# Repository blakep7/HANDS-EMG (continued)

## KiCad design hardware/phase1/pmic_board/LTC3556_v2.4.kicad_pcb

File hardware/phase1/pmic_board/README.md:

# HANDS-EMG

## Hand Activity Neural Detection using SEMG

## Project Description
A battery-powered surface electromyography (sEMG) sensor system designed to classify hand movements based on the wearer's muscle activity.
The device utilizes four channels of wet electrodes placed on the user's forearm to capture sEMG signals.
These signals are processed through our procured analog front-end module operating at a minimum of 2000 samples per second.
The digitized signals are transmitted to our microcontroller via SPI, where a machine learning algorithm classifies the hand movements based on a pre-trained model.
Our responsibilities include configuring the analog front-end module, programming a low-power microcontroller, integrating the system on a custom PCB, and training the machine learning model for accurate classification.
The system will output the movement classifications via USB, which can be visualized on a PC simulator.
Designed for efficiency, the device operates at a voltage of 3.7V provided by a rechargeable lithium polymer battery for portability.

## Contributors

- Kelly Hubbard
- Noah Marosok
- Blake Pearson
- Jayden Sumbillo
- Kirk Young

## License 📜

This project is licensed under the [Apache License 2.0](LICENSE).

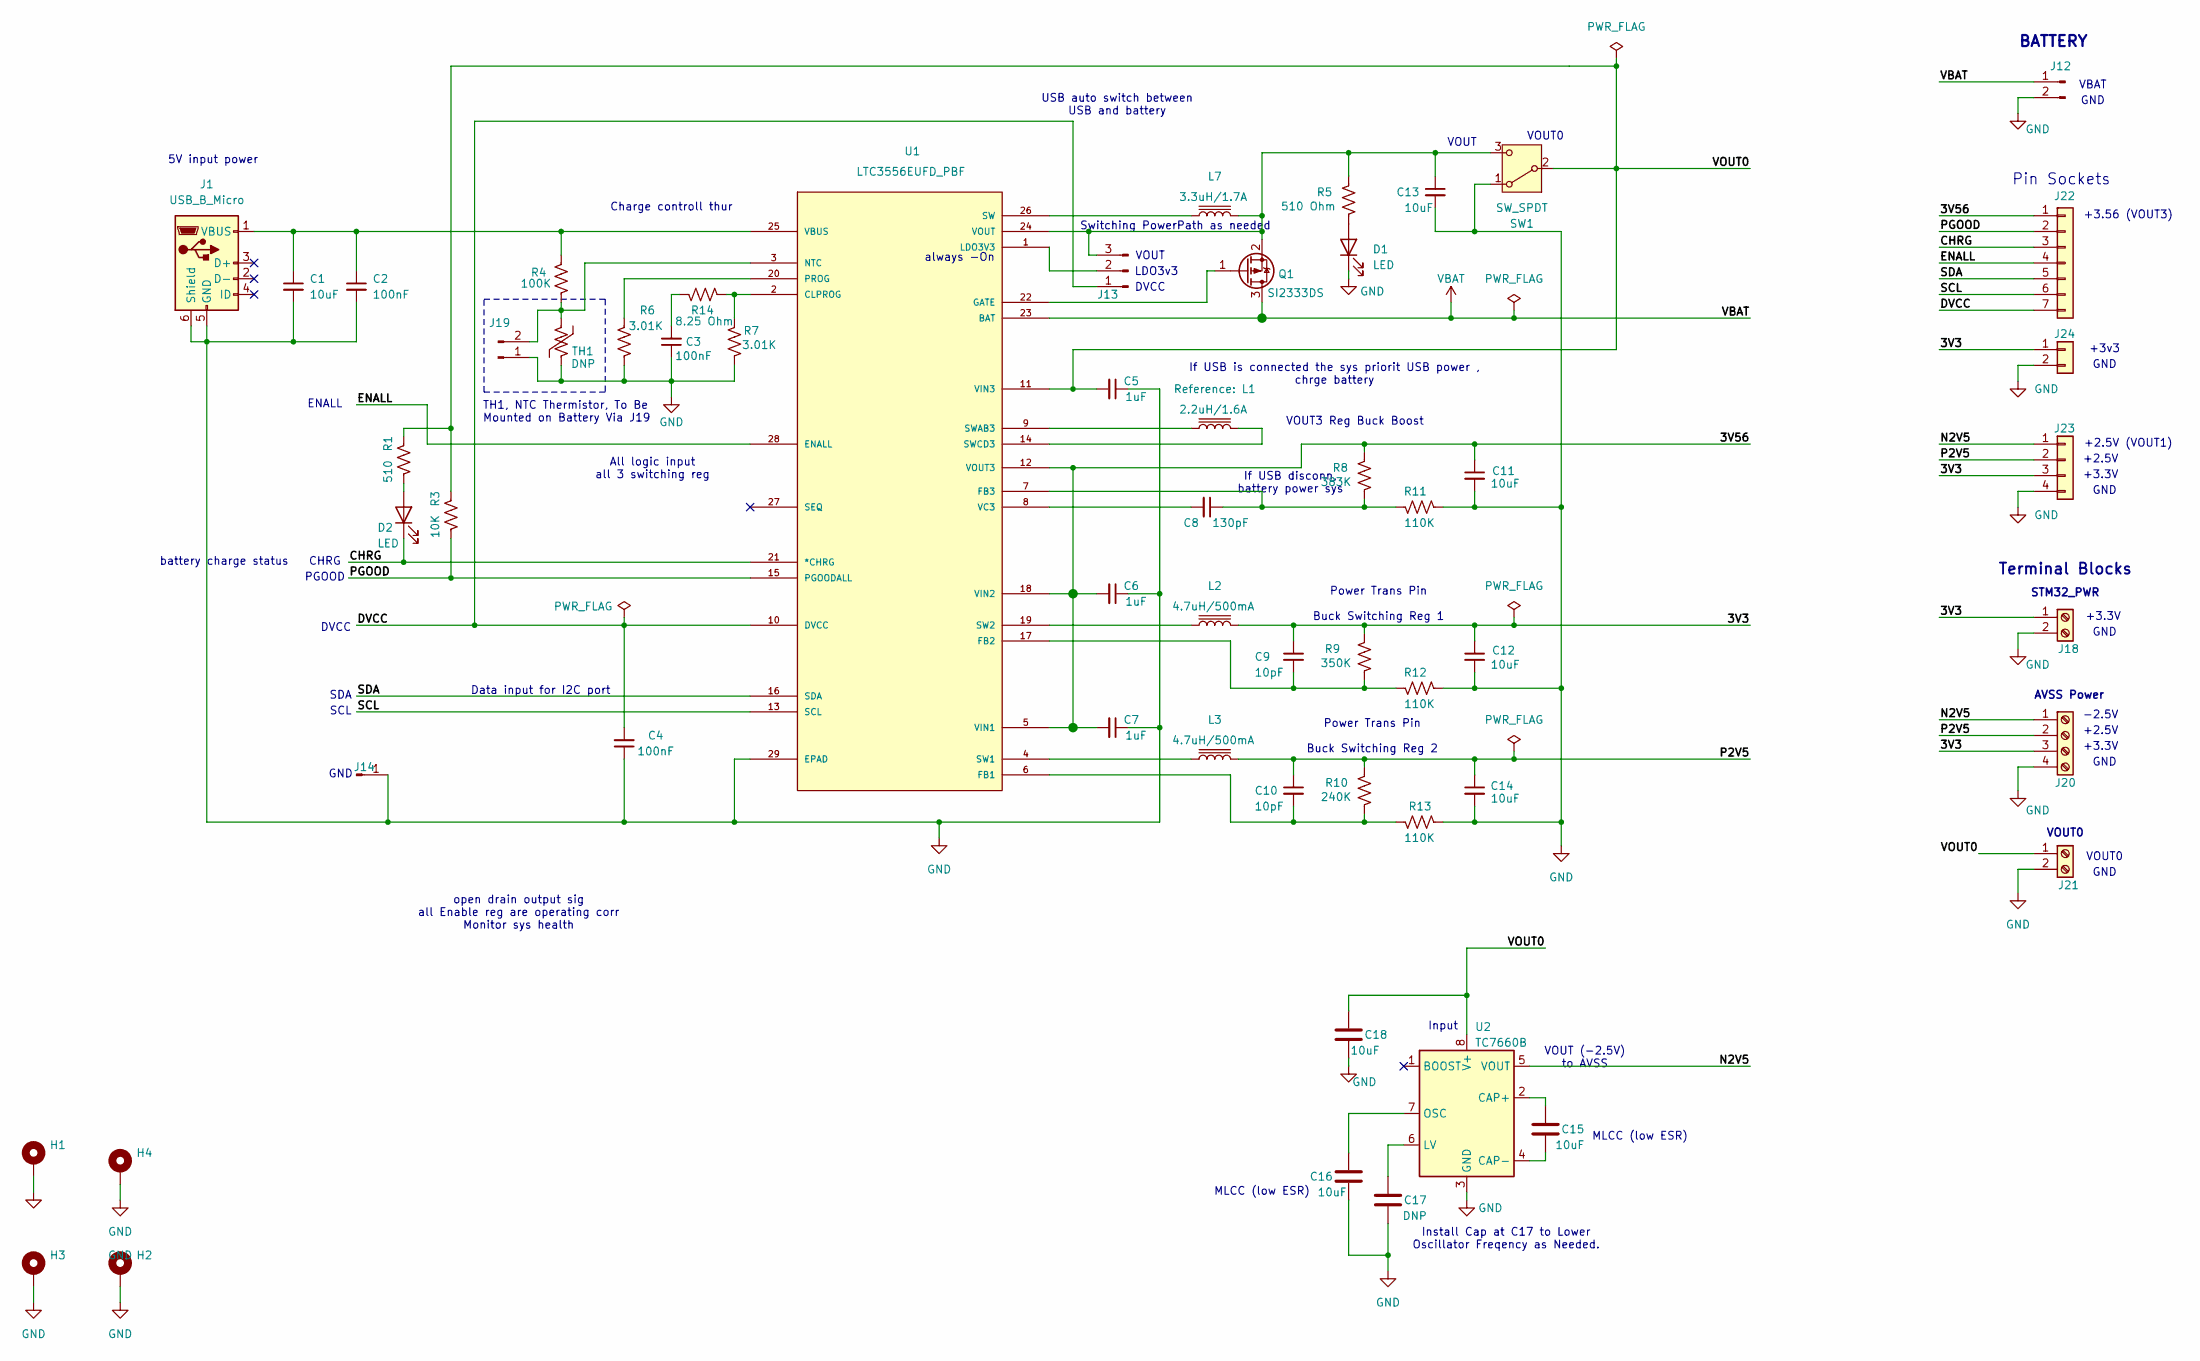
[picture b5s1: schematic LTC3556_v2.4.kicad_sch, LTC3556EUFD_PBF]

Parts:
C1: 10uF; C_1206_3216Metric
C2: 100nF; C_1206_3216Metric
C3, C4: 100nF; C_0402_1005Metric
C5, C6, C7: 1uF; C_0402_1005Metric
C8: 130pF; C_0402_1005Metric
C9, C10: 10pF; C_0402_1005Metric
C11, C12, C13, C14: 10uF; C_0402_1005Metric
C15, C16, C18: 10uF; C_0805_2012Metric_Pad1.18x1.45mm_HandSolder
C17: DNP; C_0805_2012Metric_Pad1.18x1.45mm_HandSolder
D1, D2: LED; LED_0805_2012Metric_Pad1.15x1.40mm_HandSolder
H1, H2, H3, H4: MountingHole_Pad; MountingHole_3.5mm_Pad_TopBottom
J1: USB_B_Micro; USB_Micro-B_Amphenol_10118194-0001LF_Horizontal; MPN C10418
J12: Conn_01x02_Pin; JST_PH_S2B-PH-K_1x02_P2.00mm_Horizontal; MPN C173752
J13: Conn_01x03_Pin; PinHeader_1x03_P2.54mm_Vertical; MPN C49257
J14: Conn_01x01_Pin; PinHeader_1x01_P2.54mm_Vertical; MPN C492400
J18, J21: Screw_Terminal_01x02; TerminalBlock_Phoenix_MPT-0,5-2-2.54_1x02_P2.54mm_Horizontal; MPN C474920
J19: Conn_01x02_Pin; PinHeader_1x02_P2.54mm_Vertical; MPN C225477
J20: Screw_Terminal_01x04; TerminalBlock_Phoenix_MPT-0,5-4-2.54_1x04_P2.54mm_Horizontal; MPN C474922
J22: Conn_01x07; PinSocket_1x07_P2.54mm_Vertical; MPN C2832270
J23: Conn_01x04; PinSocket_1x04_P2.54mm_Vertical; MPN C2685089
J24: Conn_01x02; PinSocket_1x02_P2.54mm_Vertical; MPN C49661
L1: 2.2uH/1.6A; L_Coilcraft_LPS4018
L2, L3: 4.7uH/500mA; L_Coilcraft_LPS3010
L7: 3.3uH/1.7A; L_Coilcraft_LPS4018
Q1: SI2333DS; SOT-23
R1: 510; R_0402_1005Metric_Pad0.72x0.64mm_HandSolder
R3: 10K; R_0402_1005Metric_Pad0.72x0.64mm_HandSolder
R4: 100K; R_0402_1005Metric_Pad0.72x0.64mm_HandSolder
R5: 510 Ohm; R_0402_1005Metric_Pad0.72x0.64mm_HandSolder
R6, R7: 3.01K; R_0402_1005Metric_Pad0.72x0.64mm_HandSolder
R8: 383K; R_0402_1005Metric_Pad0.72x0.64mm_HandSolder
R9: 350K; R_0603_1608Metric
R10: 240K; R_0402_1005Metric_Pad0.72x0.64mm_HandSolder
R11, R12, R13: 110K; R_0402_1005Metric_Pad0.72x0.64mm_HandSolder
R14: 8.25 Ohm; R_0402_1005Metric_Pad0.72x0.64mm_HandSolder
SW1: SW_SPDT; SW_Slide_SPDT_Straight_CK_OS102011MS2Q; MPN C480342
TH1: DNP; C_Disc_D3.0mm_W1.6mm_P2.50mm
U1: LTC3556EUFD_PBF; QFN-28-1EP_4x5mm_P0.5mm_EP2.65x3.65mm_ThermalVias; MANUFACTURER_PART_NUMBER ltc3556eufd#pbf; DigiKey_Part_Number 505-LTC3556EUFD#PBF-ND
U2: TC7660B; SOIC-8_3.9x4.9mm_P1.27mm; MPN C512761

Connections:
/3V3: C9.1, C12.1, J18.1, J20.3, J23.3, J24.1, L2.1, R9.1
/3V56: C6.2, C7.2, C11.1, J22.1, R8.1, U1.5 (VIN1), U1.12 (VOUT3), U1.18 (VIN2)
/CHRG: D2.1 (K), J22.3, U1.21 (*CHRG)
/DVCC: C4.2, J13.1, J22.7, U1.10 (DVCC)
/ENALL: J22.4, U1.28 (ENALL)
/N2V5: J20.1, J23.1, U2.5 (VOUT)
/P2V5: C10.1, C14.1, J20.2, J23.2, L3.1, R10.1
/PGOOD: J22.2, R3.2, U1.15 (PGOODALL)
/SCL: J22.6, U1.13 (SCL)
/SDA: J22.5, U1.16 (SDA)
/VOUT0: C5.2, C18.1, J21.1, R1.1, R3.1, SW1.2 (B), U1.11 (VIN3), U2.8 (V+)
GND: C1.2, C2.2, C3.1, C4.1, C5.1, C6.1, C7.1, C11.2, C12.2, C13.2, C14.2, C16.1, C17.2, C18.2, D1.1 (K), H1.1, H2.1, H3.1, H4.1, J1.5 (GND), J1.6 (Shield), J12.2, J14.1, J18.2, J19.1, J20.4, J21.2, J23.4, J24.2, R6.2, R7.2, R11.2, R12.2, R13.2, SW1.1 (A), TH1.1, U1.29 (EPAD), U2.3 (GND)
unnamed: C3.2, R14.2
unnamed: D1.2 (A), R5.2
unnamed: D2.2 (A), R1.2
unnamed: C1.1, C2.1, J1.1 (VBUS), R4.1, U1.25 (VBUS)
unnamed: J13.2, U1.1 (LDO3V3)
unnamed: C13.1, J13.3, L7.1, Q1.2 (S), R5.1, SW1.3 (C), U1.24 (VOUT)
unnamed: J19.2, R4.2, TH1.2, U1.3 (NTC)
unnamed: Q1.1 (G), U1.22 (GATE)
unnamed: R7.1, R14.1, U1.2 (CLPROG)
unnamed: C10.2, R10.2, R13.1, U1.6 (FB1)
unnamed: C9.2, R9.2, R12.1, U1.17 (FB2)
unnamed: C8.1, R8.2, R11.1, U1.7 (FB3)
unnamed: R6.1, U1.20 (PROG)
unnamed: L3.2, U1.4 (SW1)
unnamed: L2.2, U1.19 (SW2)
unnamed: L7.2, U1.26 (SW)
unnamed: L1.2, U1.9 (SWAB3)
unnamed: L1.1, U1.14 (SWCD3)
unnamed: C8.2, U1.8 (VC3)
unnamed: C15.1, U2.2 (CAP+)
unnamed: C15.2, U2.4 (CAP-)
unnamed: C17.1, U2.6 (LV)
unnamed: C16.2, U2.7 (OSC)
VBAT: J12.1, Q1.3 (D), U1.23 (BAT)

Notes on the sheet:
Power Trans Pin Buck Switching Reg 2
GND
+3.3V
Charge controll thur
Data input for I2C port
VOUT
AVSS Power
+2.5V
LDO3v3
BATTERY
VOUT
SDA
If USB is connected the sys priorit USB power , chrge battery
Input
MLCC (low ESR)
VOUT0
+3v3
always -On
DVCC
-2.5V
All logic input all 3 switching reg
SCL
TH1, NTC Thermistor, To Be Mounted on Battery Via J19
Terminal Blocks
5V input power
VBAT
USB auto switch between USB and battery
Switching PowerPath as needed
Power Trans Pin Buck Switching Reg 1
VOUT (-2.5V) to AVSS
If USB disconn, battery power sys
Pin Sockets
Install Cap at C17 to Lower Oscillator Freqency as Needed.
open drain output sig all Enable reg are operating corr Monitor sys health
+3.56 (VOUT3)
ENALL
STM32_PWR
battery charge status
PGOOD
+2.5V (VOUT1)

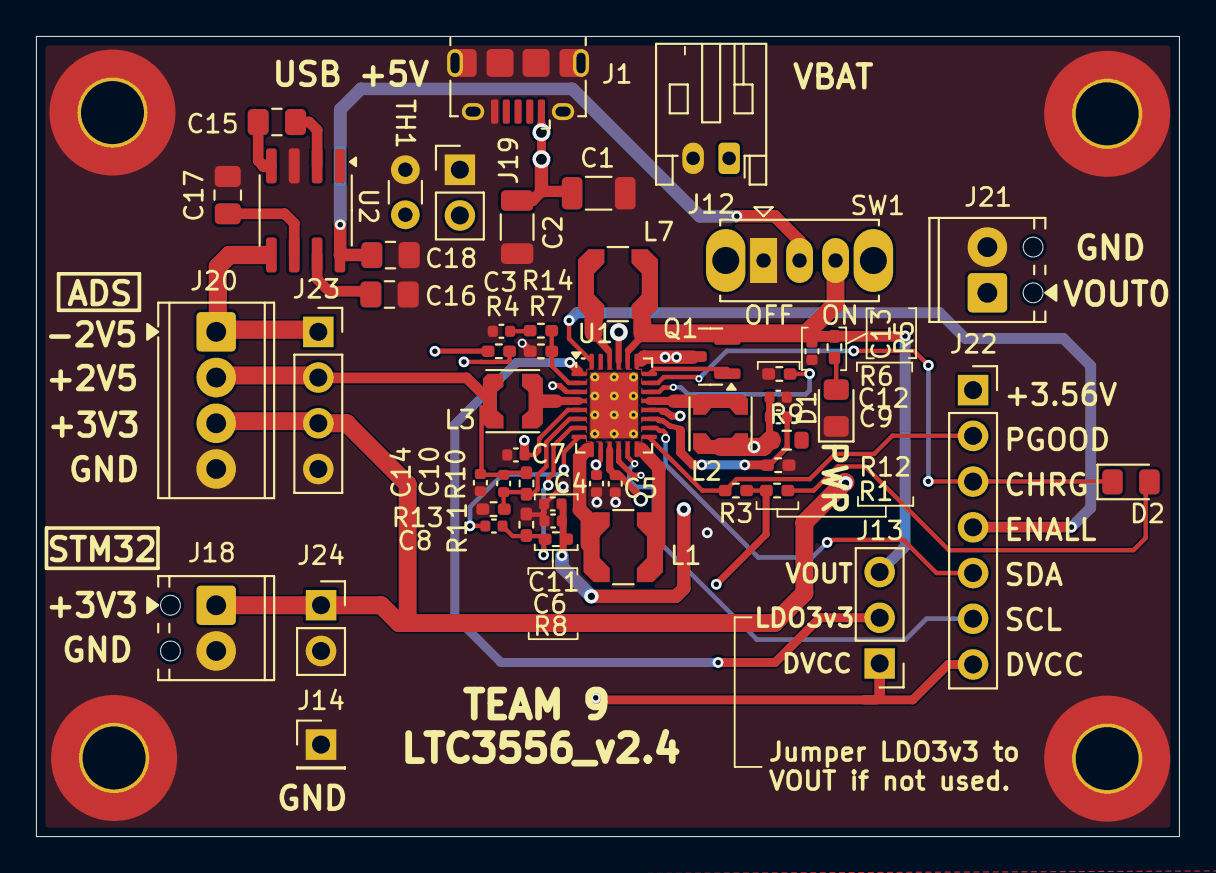
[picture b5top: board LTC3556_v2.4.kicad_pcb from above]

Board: 4 copper layers, 63.5 x 44.5 mm, 57 parts (0 on the bottom side), 36 nets.

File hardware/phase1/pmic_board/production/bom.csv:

Designator,Footprint,Quantity,Value,LCSC Part #
C1,1206,1,10uF,
"C10, C9",0402,2,10pF,
"C11, C12, C13, C14",0402,4,10uF,
"C15, C16, C18",0805,3,10uF,
C2,1206,1,100nF,
"C3, C4",0402,2,100nF,
"C5, C6, C7",0402,3,1uF,
C8,0402,1,130pF,
"D1, D2",0805,2,LED,
J1,USB_Micro-B_Amphenol_10118194-0001LF_Horizontal,1,USB_B_Micro,C10418
J12,JST_PH_S2B-PH-K_1x02_P2.00mm_Horizontal,1,Conn_01x02_Pin,C173752
J13,PinHeader_1x03_P2.54mm_Vertical,1,Conn_01x03_Pin,C49257
J14,PinHeader_1x01_P2.54mm_Vertical,1,Conn_01x01_Pin,C492400
"J18, J21","TerminalBlock_Phoenix_MPT-0,5-2-2.54_1x02_P2.54mm_Horizontal",2,Screw_Terminal_01x02,C474920
J19,PinHeader_1x02_P2.54mm_Vertical,1,Conn_01x02_Pin,C225477
J20,"TerminalBlock_Phoenix_MPT-0,5-4-2.54_1x04_P2.54mm_Horizontal",1,Screw_Terminal_01x04,C474922
J22,PinSocket_1x07_P2.54mm_Vertical,1,Conn_01x07,C2832270
J23,PinSocket_1x04_P2.54mm_Vertical,1,Conn_01x04,C2685089
J24,PinSocket_1x02_P2.54mm_Vertical,1,Conn_01x02,C49661
L1,L_Coilcraft_LPS4018,1,2.2uH/1.6A,
"L2, L3",L_Coilcraft_LPS3010,2,4.7uH/500mA,
L7,L_Coilcraft_LPS4018,1,3.3uH/1.7A,
Q1,SOT-23,1,SI2333DS,
R1,0402,1,510,
R10,0402,1,240K,
"R11, R12, R13",0402,3,110K,
R14,0402,1,8.25 Ohm,
R3,0402,1,10K,
R4,0402,1,100K,
R5,0402,1,510 Ohm,
"R6, R7",0402,2,3.01K,
R8,0402,1,383K,
R9,0603,1,350K,
SW1,SW_Slide_SPDT_Straight_CK_OS102011MS2Q,1,SW_SPDT,C480342
U1,QFN-28-1EP_4x5mm_P0.5mm_EP2.65x3.65mm_ThermalVias,1,LTC3556EUFD_PBF,C685032
U2,SOIC-8_3.9x4.9mm_P1.27mm,1,TC7660B,C512761

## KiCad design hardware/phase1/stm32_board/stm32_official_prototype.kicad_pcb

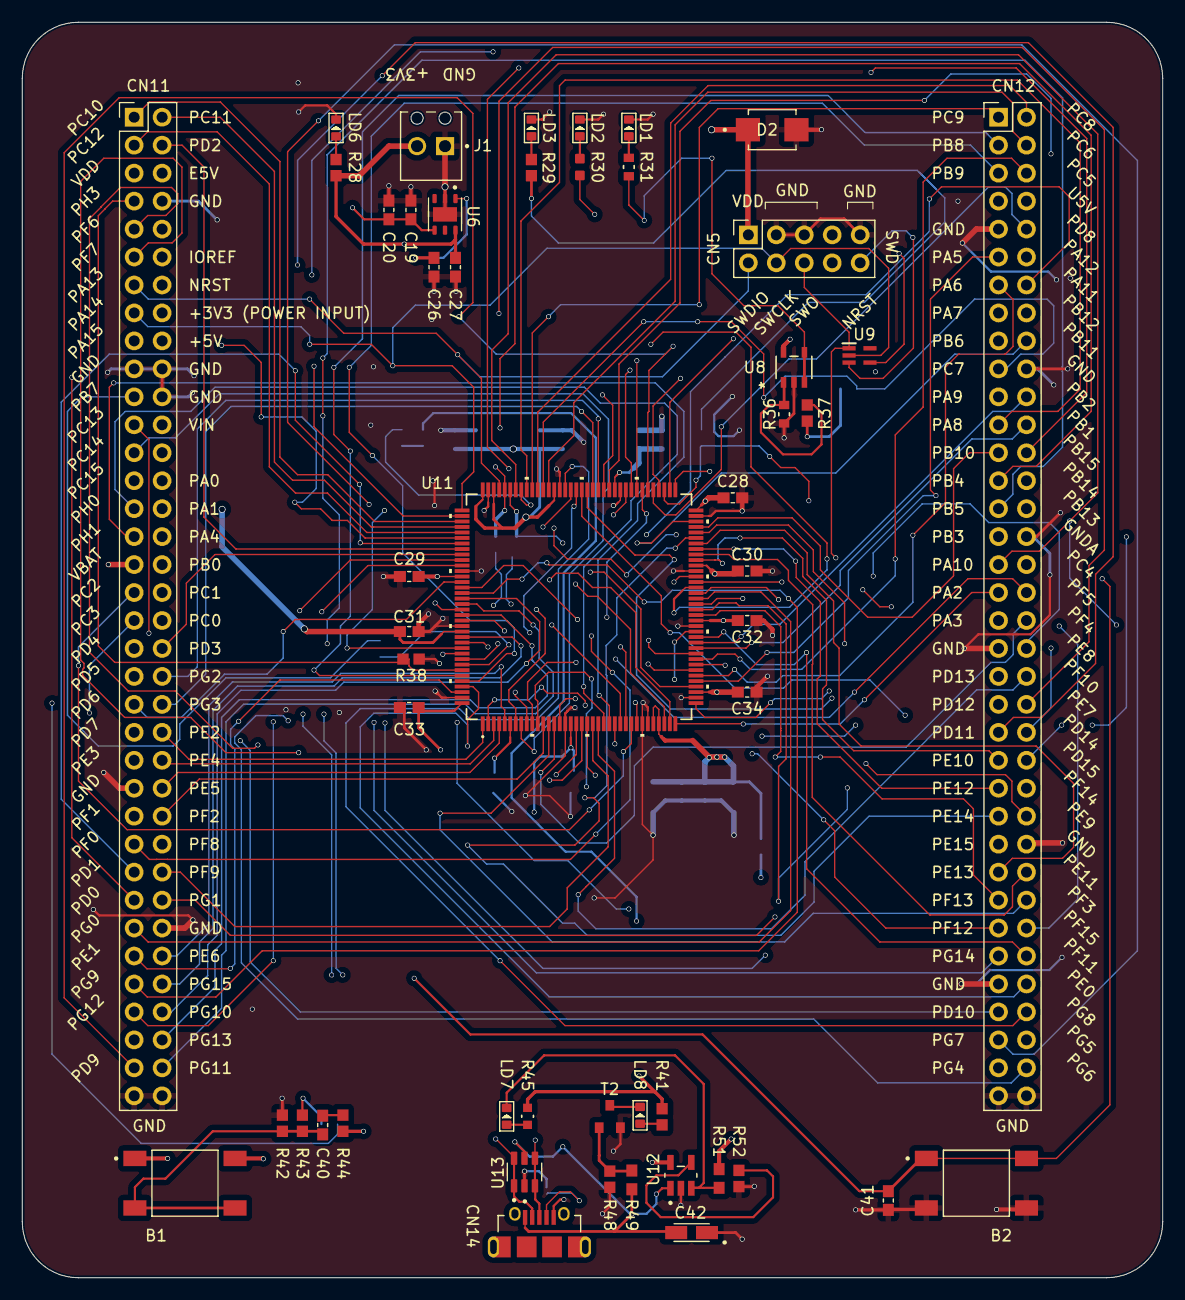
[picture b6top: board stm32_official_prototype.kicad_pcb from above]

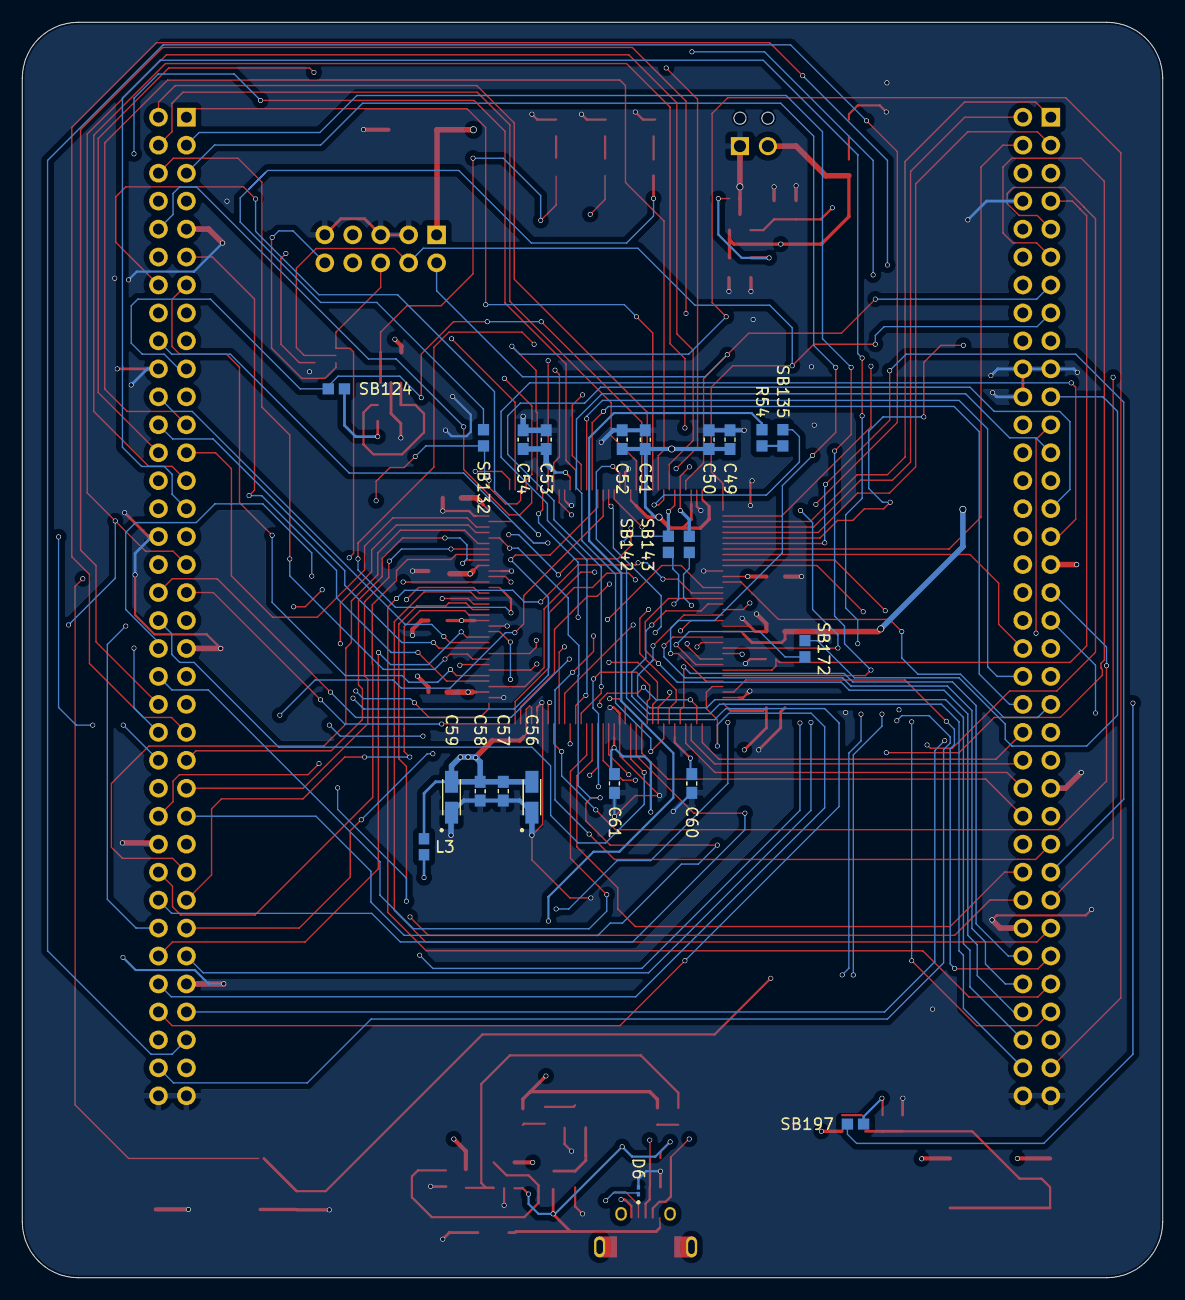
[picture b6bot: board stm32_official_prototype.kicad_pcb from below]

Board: 4 copper layers, 103.6 x 114.0 mm, 73 parts (22 on the bottom side), 136 nets.

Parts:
B1, B2: TS02-66-60-BK-160-LCR-D; SW_TS04-66-43-BK-260-SMT
C19, C27: 1uF; CAPC1608X90
C20, C26, C28, C29, C30, C31, C32, C33, C34, C41, C49, C50, C51, C53, C57, C58, C61: 100nF; CAPC1608X90
C40: [N/A]; CAPC1608X90
C42: 4.7uF; CAPMP3216X166
C52, C54: 4.7uF_X54_0603; CAPC1608X90
C56, C59: 1uF; CAPMP3216X166
C60: 1uF_X5R_0603; CAPC1608X90
CN5: Conn_ARM_JTAG_SWD_10; PinSocket_2x05_P2.54mm_Vertical
CN11, CN12: Conn_02x36_Odd_Even; PinSocket_2x36_P2.54mm_Vertical
CN14: USB_B_Micro; MOLEX_47589-1001
D2: SMLVT3V3; DIOM4336X265N
D6: ESDALC6V1-1U2; DIODE_ESDALC6V1-1U2
J1: Screw_Terminal_01x02; PHOENIX_1725656
L3: BEAD; FB0603
LD1, LD6, LD8: Green; LED-0603
LD2: Blue; LED-0603
LD3, LD7: Red; LED-0603
R28, R29: 1K; RESC1607X60N
R30: 680; R0603
R31: 510; RESC1608X60N
R36: 200K; RESC1608X60N
R37, R38, R52, R54: 10K; RESC1607X60N
R41, R43: 330; RESC1607X60N
R42: 220K; RESC1607X60N
R44: 100; RESC1607X60N
R45: 620; RC0603N_YAG
R48: 22K; RESC1607X60N
R49, R51: 47K; RESC1608X55
SB124, SB132, SB135, SB142, SB143, SB172, SB197: Closed; RESC1607X60N
T2: 9013; SOT-23
U6: LD39050PU33R; SON95P300X300X100-7N
U8: TSV631AILT; SOT23-5_STM
U9: ESDALC6V1W5; SOT65P210X110-5N
U11: STM32L496ZGTx; LQFP144-20x20mm_STM
U12: STMPS2151STR; SOT95P280X145-5N
U13: USBLC6-2SC6; SOT95P280X145-6N

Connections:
+3V3: C27.1, CN11.16, J1.2, R28.1, U6.6 (VIN)
AVDD: C56.1, C57.1, C58.1, C59.1, CN12.7, L3.2, U11.32 (VREF+), U11.33 (VDDA)
GND: B2.1, B2.4, C19.2, C20.2, C26.2, C27.2, C28.2, C29.2, C30.2, C31.2, C32.2, C33.2, C34.2, C41.2, C49.2, C50.2, C51.2, C52.2, C53.2, C54.2, C56.2, C57.2, C58.2, C59.2, C60.2, C61.2, CN5.3 (GND), CN5.5 (GND), CN5.9 (GNDDetect), CN11.8, CN11.19, CN11.20, CN11.22, CN11.49, CN11.60, CN11.71, CN11.72, CN12.9, CN12.20, CN12.32, CN12.39, CN12.54, CN12.63, CN12.71, CN12.72, CN14.5 (GND), D2.2 (A), D6.2 (A), J1.1, R36.1, R38.2, R42.1, R48.2, R52.1, T2.2, U6.2 (GND), U6.7 (GND), U8.2 (VCC-), U11.16 (VSS), U11.30 (VSSA), U11.31 (VREF-), U11.38 (VSS), U11.51 (VSS), U11.61 (VSS), U11.71 (VSS), U11.83 (VSS), U11.94 (VSS), U11.107 (VSS), U11.120 (VSS), U11.130 (VSS), U11.143 (VSS), U12.2 (GND), U13.2 (GND)
NRST: B2.2, B2.3, C41.1, CN5.10 (~RESET), CN11.14, U9.3, U11.25 (NRST)
unnamed: B1.1, B1.4, C40.1, R42.2, R43.2
unnamed: C40.2, R44.2
unnamed: R51.1, U12.3 (~FAULT)
unnamed: R29.1, SB132.2
unnamed: R37.1, SB124.2
unnamed: R43.1, SB197.2
unnamed: R48.1, R49.2, T2.1
unnamed: R54.1, SB135.2
unnamed: C26.1, U6.1 (EN)
unnamed: R36.2, R37.2, U8.1 (IN+)
unnamed: R31.1, U8.3 (IN-), U8.4 (OUT)
unnamed: SB172.1, U11.137 (PB7)
unnamed: R52.2, U12.4 (EN)
PA0: CN11.28, U11.34 (PA0)
PA1: CN11.30, U11.35 (PA1)
PA2: CN12.35, U11.36 (PA2)
PA3: CN12.37, U11.37 (PA3)
PA4: CN11.32, U11.40 (PA4)
PA5: CN12.11, U11.41 (PA5)
PA6: CN12.13, U11.42 (PA6)
PA7: CN12.15, U11.43 (PA7)
PA8: CN12.23, U11.100 (PA8)
PA9: CN12.21, SB135.1, U11.101 (PA9)
PA10: CN12.33, CN14.4 (ID), D6.1 (K), U11.102 (PA10)
PA11: CN12.14, SB142.1, U11.103 (PA11)
PA12: CN12.12, SB143.1, U11.104 (PA12)
PA13: CN5.2 (SWDIO/TMS), CN11.13, U9.4, U11.105 (PA13)
PA14: CN5.4 (SWCLK/TCK), CN11.15, U9.2, U11.109 (PA14)
PA15: CN11.17, U11.110 (PA15)
PB0: CN11.34, U11.46 (PB0)
PB1: CN12.24, U11.47 (PB1)
PB2: CN12.22, U11.48 (PB2)
PB3: CN5.6 (SWO/TDO), CN12.31, U9.1, U11.133 (PB3)
PB4: CN12.27, U11.134 (PB4)
PB5: CN12.29, U11.135 (PB5)
PB6: CN12.17, U11.136 (PB6)
PB7: CN11.21, R30.1, SB172.2
PB8: CN12.3, U11.139 (PB8)
PB9: CN12.5, U11.140 (PB9)
PB10: CN12.25, U11.69 (PB10)
PB11: CN12.18, U11.70 (PB11)
PB12: CN12.16, U11.73 (PB12)
PB13: CN12.30, U11.74 (PB13)
PB14: CN12.28, SB132.1, U11.75 (PB14)
PB15: CN12.26, U11.76 (PB15)
PC0: CN11.38, U11.26 (PC0)
PC1: CN11.36, U11.27 (PC1)
PC2: CN11.35, U11.28 (PC2)
PC3: CN11.37, U11.29 (PC3)
PC4: CN12.34, U11.44 (PC4)
PC5: CN12.6, U11.45 (PC5)
PC6: CN12.4, U11.96 (PC6)
PC7: CN12.19, SB124.1, U11.97 (PC7)
PC8: CN12.2, U11.98 (PC8)
PC9: CN12.1, U11.99 (PC9)
PC10: CN11.1, U11.111 (PC10)
PC11: CN11.2, U11.112 (PC11)
PC12: CN11.3, U11.113 (PC12)
PC13: CN11.23, SB197.1, U11.7 (PC13)
PC14: CN11.25, U11.8 (PC14)
PC15: CN11.27, U11.9 (PC15)
PD0: CN11.57, U11.114 (PD0)
PD1: CN11.55, U11.115 (PD1)
PD2: CN11.4, U11.116 (PD2)
PD3: CN11.40, U11.117 (PD3)
PD4: CN11.39, U11.118 (PD4)
PD5: CN11.41, U11.119 (PD5)
PD6: CN11.43, U11.122 (PD6)
PD7: CN11.45, U11.123 (PD7)
PD8: CN12.10, U11.77 (PD8)
PD9: CN11.69, U11.78 (PD9)
PD10: CN12.65, U11.79 (PD10)
PD11: CN12.45, U11.80 (PD11)
PD12: CN12.43, U11.81 (PD12)
PD13: CN12.41, U11.82 (PD13)
PD14: CN12.46, U11.85 (PD14)
PD15: CN12.48, U11.86 (PD15)
PE0: CN12.64, U11.141 (PE0)
PE1: CN11.61, U11.142 (PE1)
PE2: CN11.46, U11.1 (PE2)
PE3: CN11.47, U11.2 (PE3)
PE4: CN11.48, U11.3 (PE4)
PE5: CN11.50, U11.4 (PE5)
PE6: CN11.62, U11.5 (PE6)
PE7: CN12.44, U11.58 (PE7)
PE8: CN12.40, U11.59 (PE8)
PE9: CN12.52, U11.60 (PE9)
PE10: CN12.47, U11.63 (PE10)
PE11: CN12.56, U11.64 (PE11)
PE12: CN12.49, U11.65 (PE12)
PE13: CN12.55, U11.66 (PE13)
PE14: CN12.51, U11.67 (PE14)
PE15: CN12.53, U11.68 (PE15)
PF0: CN11.53, U11.10 (PF0)
PF1: CN11.51, U11.11 (PF1)
PF2: CN11.52, U11.12 (PF2)
PF3: CN12.58, U11.13 (PF3)
PF4: CN12.38, U11.14 (PF4)
PF5: CN12.36, U11.15 (PF5)
PF6: CN11.9, U11.18 (PF6)
PF7: CN11.11, U11.19 (PF7)
PF8: CN11.54, U11.20 (PF8)
PF9: CN11.56, U11.21 (PF9)
PF10: CN12.42, U11.22 (PF10)
PF11: CN12.62, U11.49 (PF11)
PF12: CN12.59, U11.50 (PF12)
PF13: CN12.57, U11.53 (PF13)
PF14: CN12.50, U11.54 (PF14)
PF15: CN12.60, U11.55 (PF15)
PG0: CN11.59, U11.56 (PG0)
PG1: CN11.58, U11.57 (PG1)
PG2: CN11.42, U11.87 (PG2)
PG3: CN11.44, U11.88 (PG3)
PG4: CN12.69, U11.89 (PG4)
PG5: CN12.68, U11.90 (PG5)
PG6: CN12.70, U11.91 (PG6)
PG7: CN12.67, U11.92 (PG7)
PG8: CN12.66, U11.93 (PG8)
PG9: CN11.63, U11.124 (PG9)
PG10: CN11.66, U11.125 (PG10)
PG11: CN11.70, U11.126 (PG11)
PG12: CN11.65, U11.127 (PG12)
PG13: CN11.68, U11.128 (PG13)
PG14: CN12.61, U11.129 (PG14)
PG15: CN11.64, U11.132 (PG15)
PH0: CN11.29, U11.23 (PH0)
PH1: CN11.31, U11.24 (PH1)
PH3-BOOT0: CN11.7, R38.1, U11.138 (PH3)
USB_DN: CN14.2 (D-), SB142.2, U13.1 (I/O1), U13.6 (I/O1)
USB_DP: CN14.3 (D+), SB143.2, U13.3 (I/O2), U13.4 (I/O2)
USB_VBUS: CN14.1 (VBUS), R49.1, R54.2, U12.1 (OUT), U13.5 (VBUS)
VDD: B1.2, B1.3, C19.1, C20.1, C28.1, C29.1, C30.1, C31.1, C32.1, C33.1, C34.1, C49.1, C50.1, C51.1, C52.1, C53.1, C54.1, C60.1, C61.1, CN5.1 (VTref), CN11.5, CN11.33, D2.1 (K), L3.1, R41.2, R44.1, R45.2, R51.2, U6.4 (VOUT), U8.5 (VCC+), U11.6 (VBAT), U11.17 (VDD), U11.39 (VDD), U11.52 (VDD), U11.62 (VDD), U11.72 (VDD), U11.84 (VDD), U11.95 (VDDIO2), U11.106 (VDDUSB), U11.108 (VDD), U11.121 (VDD), U11.131 (VDDIO2), U11.144 (VDD), U12.5 (IN)

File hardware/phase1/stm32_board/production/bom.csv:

Designator,Footprint,Quantity,Value,LCSC Part #
"B1, B2",SW_TS04-66-43-BK-260-SMT,2,TS02-66-60-BK-160-LCR-D,
"C19, C27",CAPC1608X90,2,1uF,
"C20, C26, C28, C29, C30, C31, C32, C33, C34, C41, C49, C50, C51, C53, C57, C58, C61",CAPC1608X90,17,100nF,
C40,CAPC1608X90,1,[N/A],
C42,CAPMP3216X166,1,4.7uF,
"C52, C54",CAPC1608X90,2,4.7uF_X54_0603,
"C56, C59",CAPMP3216X166,2,1uF,
C60,CAPC1608X90,1,1uF_X5R_0603,
"CN11, CN12",PinSocket_2x36_P2.54mm_Vertical,2,Conn_02x36_Odd_Even,
CN14,MOLEX_47589-1001,1,USB_B_Micro,
CN5,PinSocket_2x05_P2.54mm_Vertical,1,Conn_ARM_JTAG_SWD_10,
D2,DIOM4336X265N,1,SMLVT3V3,
D6,DIODE_ESDALC6V1-1U2,1,ESDALC6V1-1U2,
J1,PHOENIX_1725656,1,Screw_Terminal_01x02,
L3,FB0603,1,BEAD,
"LD1, LD6, LD8",LED-0603,3,Green,
LD2,LED-0603,1,Blue,
"LD3, LD7",LED-0603,2,Red,
"R28, R29",RESC1607X60N,2,1K,
R30,R0603,1,680,
R31,RESC1608X60N,1,510,
R36,RESC1608X60N,1,200K,
"R37, R38, R52, R54",RESC1607X60N,4,10K,
"R41, R43",RESC1607X60N,2,330,
R42,RESC1607X60N,1,220K,
R44,RESC1607X60N,1,100,
R45,RC0603N_YAG,1,620,
R48,RESC1607X60N,1,22K,
"R49, R51",RESC1608X55,2,47K,
"SB124, SB132, SB135, SB142, SB143, SB172, SB197",RESC1607X60N,7,Closed,
T2,SOT-23,1,9013,
U11,LQFP144-20x20mm_STM,1,STM32L496ZGTx,
U12,SOT95P280X145-5N,1,STMPS2151STR,
U13,SOT95P280X145-6N,1,USBLC6-2SC6,
U6,SON95P300X300X100-7N,1,LD39050PU33R,
U8,SOT23-5_STM,1,TSV631AILT,
U9,SOT65P210X110-5N,1,ESDALC6V1W5,
